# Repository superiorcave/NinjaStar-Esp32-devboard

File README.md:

# NinjaStar-Esp32-devboard
A custom created Esp32 devboard in the shape of a ninja star. This board also comes fitted with several classic images from the Anime.
Using an Esp32 Wroom, I was able to create a fun shape for the classic devboard and even insert my own custom images. Fitted with custom LEDS and buttons, 
this is great mircocontroller for any project.

Download the production folder and use the zip file to find the Gerber files for production.

Click the Link Below to view my journal:
https://blueprint.hackclub.com/projects/2972

### Schematic Image

### PCB Image

### Gerber Viewer (From JLC PCB)

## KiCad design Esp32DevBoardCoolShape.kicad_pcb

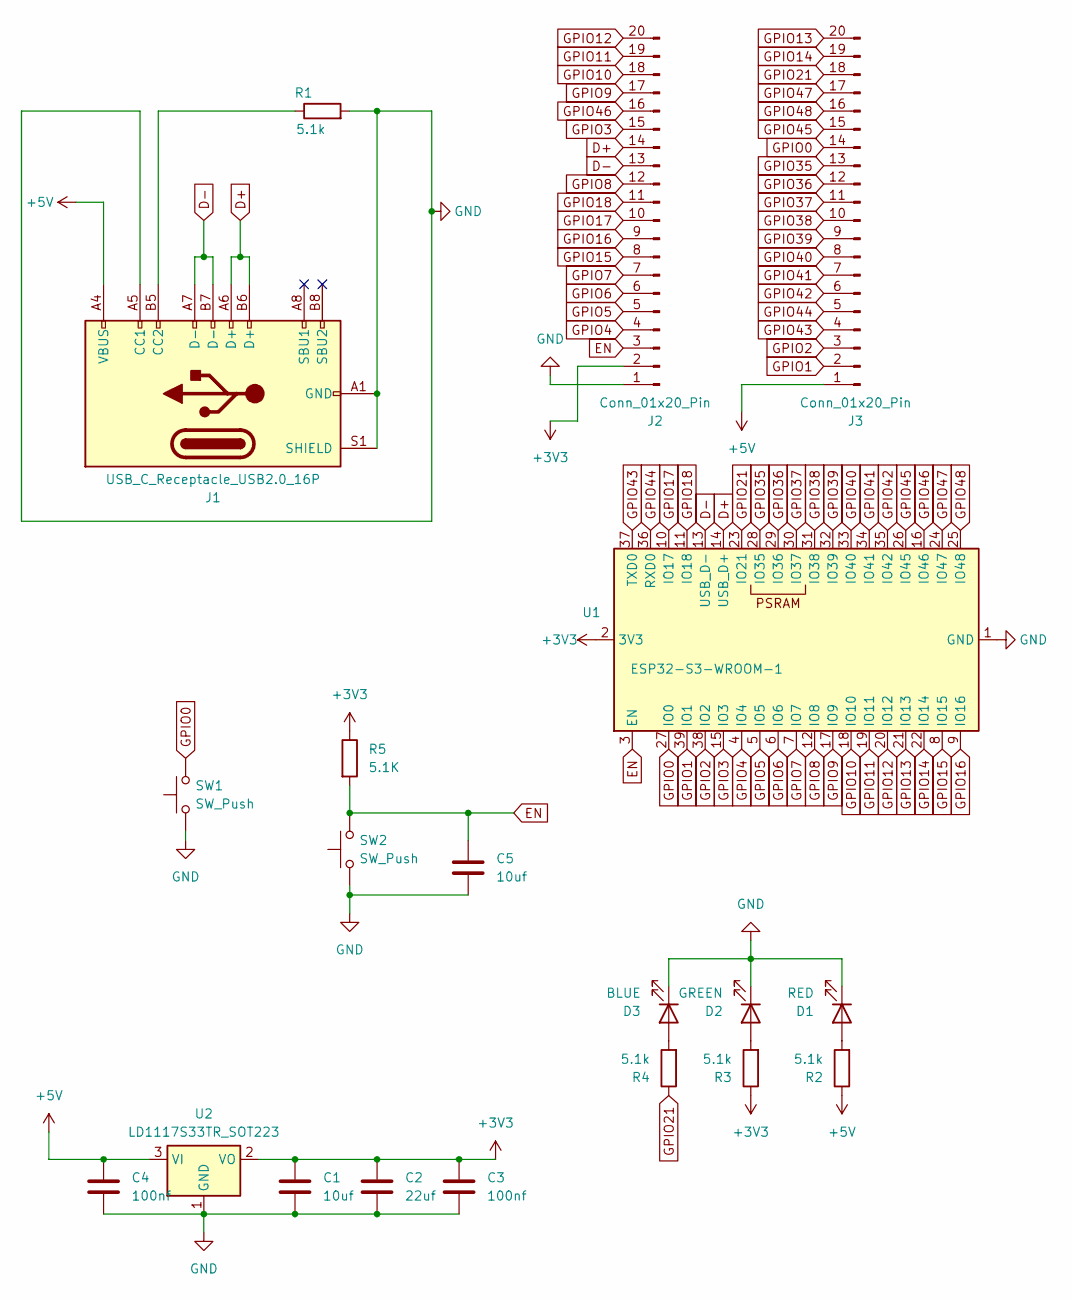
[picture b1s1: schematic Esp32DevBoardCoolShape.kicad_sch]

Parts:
C1, C5: 10uf; C_1206_3216Metric_Pad1.33x1.80mm_HandSolder
C2: 22uf; C_1206_3216Metric_Pad1.33x1.80mm_HandSolder
C3, C4: 100nf; C_0603_1608Metric_Pad1.08x0.95mm_HandSolder
D1: RED; LED_0805_2012Metric_Pad1.15x1.40mm_HandSolder
D2: GREEN; LED_0805_2012Metric_Pad1.15x1.40mm_HandSolder
D3: BLUE; LED_0805_2012Metric_Pad1.15x1.40mm_HandSolder
J1: USB_C_Receptacle_USB2.0_16P; USB_C_Receptacle_HCTL_HC-TYPE-C-16P-01A
J2, J3: Conn_01x20_Pin; PinHeader_1x20_P2.00mm_Vertical
R1, R2, R3, R4: 5.1k; R_0603_1608Metric_Pad0.98x0.95mm_HandSolder
R5: 5.1K; R_0603_1608Metric_Pad0.98x0.95mm_HandSolder
SW1, SW2: SW_Push; SW_SPST_B3S-1000
U1: ESP32-S3-WROOM-1
U2: LD1117S33TR_SOT223; SOT-223-3_TabPin2

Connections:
+3V3: C1.1, C2.1, C3.1, J2.2, R3.1, R5.1, U1.2 (3V3), U2.2 (VO)
+5V: C4.1, J1.A4 (VBUS), J1.A9 (VBUS), J1.B4 (VBUS), J1.B9 (VBUS), J3.1, R2.1, U2.3 (VI)
D+: J1.A6 (D+), J1.B6 (D+), J2.14, U1.14 (USB_D+)
D-: J1.A7 (D-), J1.B7 (D-), J2.13, U1.13 (USB_D-)
EN: C5.1, J2.3, R5.2, SW2.2, U1.3 (EN)
GND: C1.2, C2.2, C3.2, C4.2, C5.2, D1.1 (K), D2.1 (K), D3.1 (K), J1.A1 (GND), J1.A5 (CC1), J1.A12 (GND), J1.B1 (GND), J1.B12 (GND), J1.S1 (SHIELD), J2.1, R1.2, SW1.1, SW2.1, U1.1 (GND), U1.40 (GND), U1.41 (GND), U2.1 (GND)
GPIO0: J3.14, SW1.2, U1.27 (IO0)
GPIO1: J3.2, U1.39 (IO1)
GPIO2: J3.3, U1.38 (IO2)
GPIO3: J2.15, U1.15 (IO3)
GPIO4: J2.4, U1.4 (IO4)
GPIO5: J2.5, U1.5 (IO5)
GPIO6: J2.6, U1.6 (IO6)
GPIO7: J2.7, U1.7 (IO7)
GPIO8: J2.12, U1.12 (IO8)
GPIO9: J2.17, U1.17 (IO9)
GPIO10: J2.18, U1.18 (IO10)
GPIO11: J2.19, U1.19 (IO11)
GPIO12: J2.20, U1.20 (IO12)
GPIO13: J3.20, U1.21 (IO13)
GPIO14: J3.19, U1.22 (IO14)
GPIO15: J2.8, U1.8 (IO15)
GPIO16: J2.9, U1.9 (IO16)
GPIO17: J2.10, U1.10 (IO17)
GPIO18: J2.11, U1.11 (IO18)
GPIO21: J3.18, R4.1, U1.23 (IO21)
GPIO35: J3.13, U1.28 (IO35)
GPIO36: J3.12, U1.29 (IO36)
GPIO37: J3.11, U1.30 (IO37)
GPIO38: J3.10, U1.31 (IO38)
GPIO39: J3.9, U1.32 (IO39)
GPIO40: J3.8, U1.33 (IO40)
GPIO41: J3.7, U1.34 (IO41)
GPIO42: J3.6, U1.35 (IO42)
GPIO43: J3.4, U1.37 (TXD0)
GPIO44: J3.5, U1.36 (RXD0)
GPIO45: J3.15, U1.26 (IO45)
GPIO46: J2.16, U1.16 (IO46)
GPIO47: J3.17, U1.24 (IO47)
GPIO48: J3.16, U1.25 (IO48)
unnamed: D1.2 (A), R2.2
unnamed: D2.2 (A), R3.2
unnamed: D3.2 (A), R4.2
unnamed: J1.B5 (CC2), R1.1

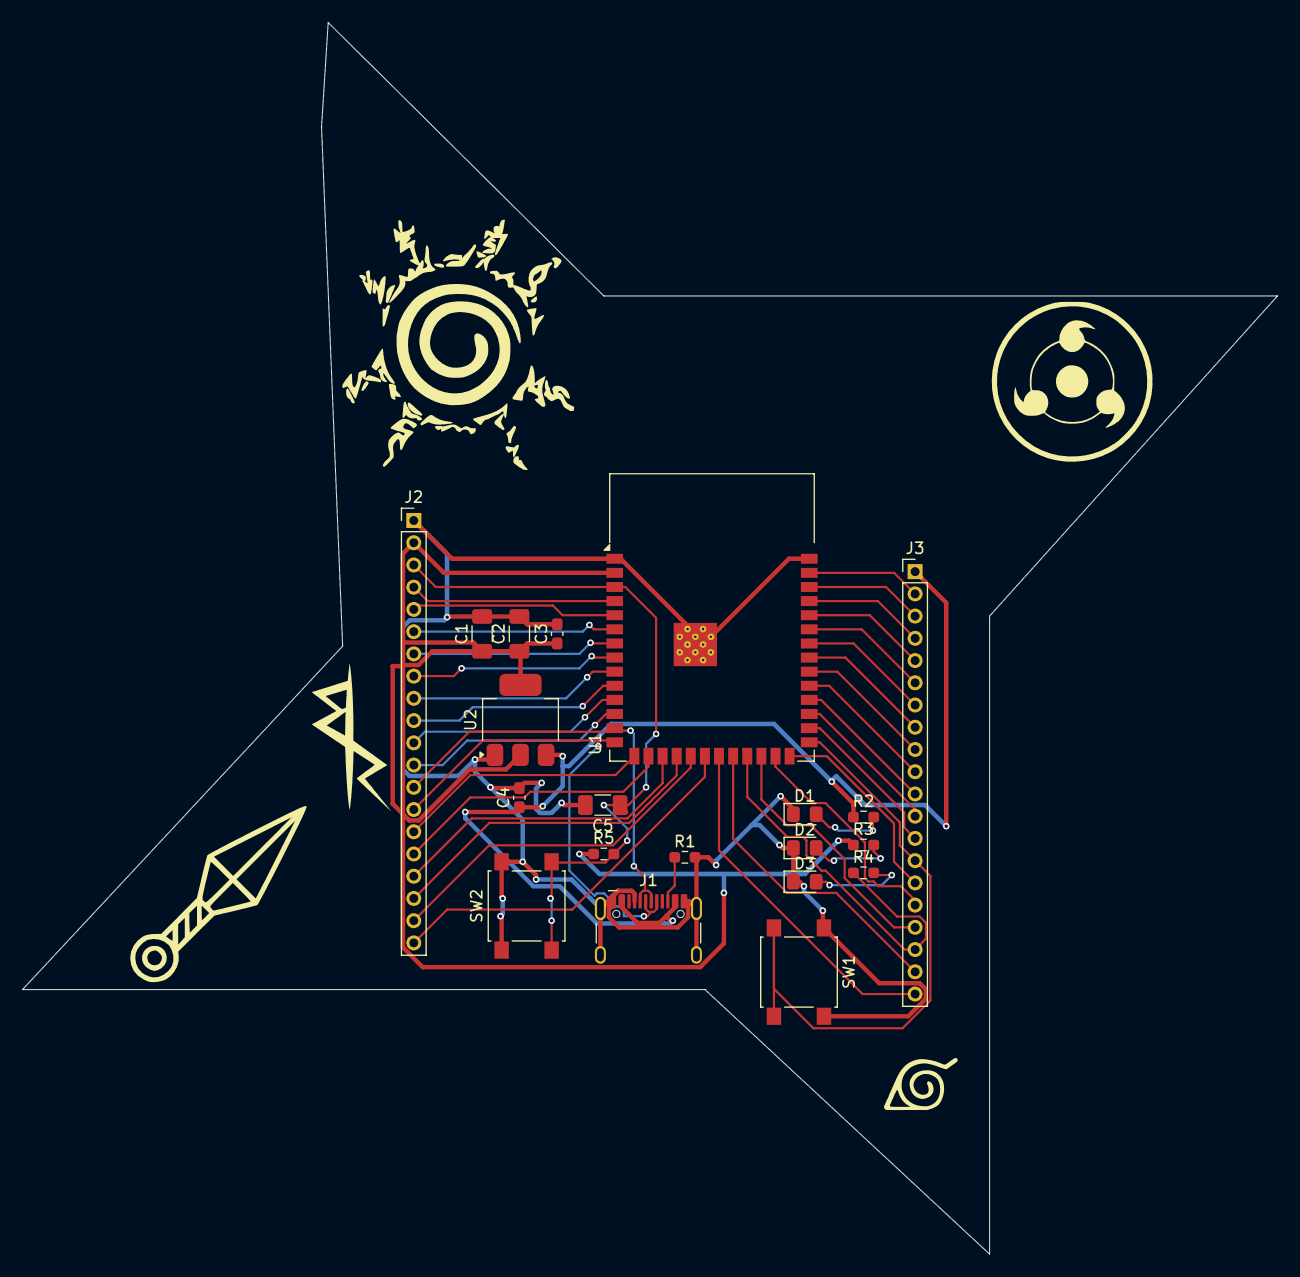
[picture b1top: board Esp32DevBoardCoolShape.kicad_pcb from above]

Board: 2 copper layers, 112.9 x 110.8 mm, 20 parts (0 on the bottom side), 44 nets.

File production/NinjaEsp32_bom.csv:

Designator,Footprint,Quantity,Value,LCSC Part #
"C1, C5",1206,2,10uf,
C2,1206,1,22uf,
"C3, C4",0603,2,100nf,
D1,0805,1,RED,
D2,0805,1,GREEN,
D3,0805,1,BLUE,
J1,USB_C_Receptacle_HCTL_HC-TYPE-C-16P-01A,1,USB_C_Receptacle_USB2.0_16P,
"J2, J3",PinHeader_1x20_P2.00mm_Vertical,2,Conn_01x20_Pin,
"R1, R2, R3, R4, R5",0603,5,5.1k,
"SW1, SW2",SW_SPST_B3S-1000,2,SW_Push,
U1,ESP32-S3-WROOM-1,1,ESP32-S3-WROOM-1,
U2,SOT-223-3_TabPin2,1,LD1117S33TR_SOT223,

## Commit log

2025-12-03 Enhance README with project details and images
    Added detailed project description, images, and links.
2025-12-03 Update README with production folder download info
    Added download instructions for production files.
2025-12-03 Kicad FIles
